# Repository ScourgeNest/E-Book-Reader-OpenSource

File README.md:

# 📖 OpenBook - Open-Source E-Book Reader

# Description
OpenBook is an open-source project aimed at developing an affordable and easily manufacturable e-book reader. This repository contains all the necessary hardware design files, including schematics, PCB layouts, 3D models, and manufacturing files.

#  Table of Contents

1. [📝 Description](#description)
2. [📜 Table of Contents](#table-of-contents)
3. [📂 Repository Contents](#repository-contents)
4. [🎯 Target Audience](#target-audience)
5. [🚀 Project Overview & Features](#project-overview--features)
6. [📊 E-Book Reader Diagram](#e-book-reader-diagram)
7. [📦 Bill of Materials (BOM)](#bill-of-materials-bom)
8. [🔧 Hardware Functionality Description](#hardware-functionality-description)
9. [🔌 Communication Interfaces](#communication-interfaces)
10. [⚡ Components and Estimated Power Consumption](#components-and-estimated-power-consumption)
11. [⚙️ ESP32-C6 Pin Usage Breakdown](#esp32-c6-pin-usage-breakdown)
12. [🛠️ Implementation Steps](#implementation-steps)
13. [🔧 Finalizing the Project](#finalizing-the-project)
14. [🖼️ Images](#images)

# Repository Contents
- 📡 **Schematic & PCB Design** → Circuit design files (`.sch`, `.brd`).
- 🏭 **Manufacturing Files** → Gerber files, Bill of Materials (BOM), Pick & Place files.
- 🏗️ **3D Model & Mechanical Design** → Full 3D assembly of the device, including PCB, battery, display, and casing.
- 📷 **Renders & Images** → Visual representations of the final device and PCB layout.
- 📜 **Documentation** → Detailed explanation of hardware architecture, component connections, and design decisions.

# Target Audience
This project is intended for hardware developers, electronics engineers, and open-source enthusiasts interested in PCB design, e-paper displays, and embedded systems.

## Project Overview & Features

### 📌 Project Goal
OpenBook aims to create an accessible and customizable open-source e-book reader that is affordable and easy to manufacture. By leveraging open hardware and software, we enable users to build and modify their own e-book readers while maintaining a low production cost.

### 🔹 Key Features
- **ESP32-C6 based** – Low-power microcontroller with Wi-Fi & Bluetooth connectivity.
- **E-paper Display** – Energy-efficient and easy on the eyes for long reading sessions.
- **Expandable Storage** – Supports microSD cards for storing a large collection of e-books.
- **USB-C Charging** – Modern and fast charging capability.
- **Open-Source Hardware** – Complete design files available for customization.
- **Compact and Lightweight** – Optimized design for portability and comfort.

### 🔧 System Architecture
The OpenBook device consists of four main components:
1. **PCB & Electronics** – The ESP32-C6 microcontroller, display driver, power management, and storage.
2. **E-paper Display Module** – A low-power display for efficient reading.
3. **Enclosure & Mechanical Design** – A 3D-printed or injection-molded case housing all components securely.
4. **Polymer Lithium-Ion Battery** – A rechargeable battery providing power to the device.

#  E-Book Reader Diagram

# Bill of Materials (BOM)

| 🔩 Component                                        | 🔗 Link                | 📄 Datasheet                        |
|--------------------------------------------------|-----------------------------------|-----------------------------------|
| ESP32-C6 WROOM-1-N8                              | [SnapMagic](https://www.snapeda.com/parts/ESP32-C6-WROOM-1-N8/Espressif+Systems/view-part/?ref=eda)         | [Datasheet](https://www.snapeda.com/parts/ESP32-C6-WROOM-1-N8/Espressif%20Systems/datasheet/)     |
| ESP32C6 Varistor 1812                            | [Mouser](https://ro.mouser.com/ProductDetail/EPCOS-TDK/B72520T0350K062?qs=dEfas%2FXlABIszF52uu7vrg%3D%3D)        | [Datasheet](https://www.tdk-electronics.tdk.com/inf/75/db/CTVS_14/Surge_protection_series.pdf)     |
| ESP32 WROVER 0805 Capacitor                      | [Mouser](https://ro.mouser.com/ProductDetail/KYOCERA-AVX/SD0805S020S1R0?qs=jCA%252BPfw4LHbpkAoSnwrdjw%3D%3D)         | [Datasheet](https://ro.mouser.com/datasheet/2/40/schottky-3165252.pdf)     |
| ESP32 WROVER BME680 Sensor                       | [SnapMagic](https://www.snapeda.com/parts/BME680/Bosch/view-part/?welcome=home)        | [Datasheet](https://www.snapeda.com/parts/BME680/Bosch%20Sensortec/datasheet/)     |
| ESP32 WROVER MCP73831 Power Management           | [Mouser](https://eu.mouser.com/ProductDetail/Microchip-Technology/MCP73831T-2ACI-OT?qs=yUQqVecv4qvbBQBGbHx0Mw%3D%3D)         | [Datasheet](https://eu.mouser.com/datasheet/2/268/MCP73831_Family_Data_Sheet_DS20001984H-3441711.pdf)     || ESP32 WROVER P-Channel MOSFET                    | [Component Search Engine](https://componentsearchengine.com/part-view/DMG2305UX-7/Diodes%20Incorporated)         | [Datasheet](https://www.diodes.com//assets/Datasheets/DMG2305UX.pdf)     |
| LED Chip 0603                                    | [SnapMagic](https://www.snapeda.com/parts/KP-1608SURCK/Kingbright/view-part/?ref=search&t=LED%200603)        | [Datasheet](https://www.snapeda.com/parts/KP-1608SURCK/Kingbright/datasheet/)     |
| SJ                                               | [GrabCad](https://grabcad.com/library/solder-jumpers-1)         | [Datasheet](https://www.youtube.com/watch?v=dQw4w9WgXcQ)     |
| LTSPICE Resistor 0402                            | [Component Search Engine](https://componentsearchengine.com/part-view/R0402%201%25%20100%20K%20(RC0402FR-07100KL)/YAGEO)        | [Datasheet](https://www.yageo.com/upload/media/product/products/datasheet/rchip/PYu-RC_Group_51_RoHS_L_12.pdf)     |
| RCL CPOL 3528                                    | [SnapMagic](https://www.snapeda.com/parts/TAJB475K025RNJ/AVX/view-part/?ref=dk&t=capacitor%203528&con_ref=None)        | [Datasheet](https://s3.amazonaws.com/snapeda/datasheet/TAJB475K025RNJ_AVX.pdf)     |
| 112A-TAAR-R03                                    | [Comet](https://store.comet.srl.ro/Catalogue/Product/43497/)         | [Datasheet](https://store.comet.bg/download-file.php?id=27596)     |
| Capacitor 0402                                   | [Component Search Engine](https://componentsearchengine.com/part-view/CC0402MRX5R5BB106/YAGEO)         | [Datasheet](https://componentsearchengine.com/Datasheets/2/CC0402MRX5R5BB106.pdf)     |
| 744043680 IND                                    | [Mouser](https://eu.mouser.com/ProductDetail/Wurth-Elektronik/744043680?qs=PGXP4M47uW6VkZq%252BkzjrHA%3D%3D)        | [Datasheet](https://www.we-online.com/components/products/datasheet/744043680.pdf)     |
| BD5229G-TR                                       | [Component Search Engine](https://componentsearchengine.com/part-view/BD5229G-TR/ROHM%20Semiconductor)         | [Datasheet](https://datasheet.datasheetarchive.com/originals/distributors/Datasheets_SAMA/f2b9741ef86007909f138d561a359946.pdf)     |
| Custom Button                                    | [Panasonic](https://industry.panasonic.com/global/en/products/control/switch/light-touch/number/evqpuj02k)        | [Datasheet](https://industry.panasonic.com/global/en/downloads?tab=catalog&small_g_cd=203&part_no=EVQPUJ02K&q=RVZRUFVKMDJLJTdDMTMlN0MyMDMlN0MzNDU5JTdDMSU3QyU3QzIlN0M%3D)     |
| CPH3225A                                         | [SnapMagic](https://www.snapeda.com/parts/CPH3225A/Seiko+Instruments/view-part/?ref=eda)         | [Datasheet](https://www.snapeda.com/parts/CPH3225A/Seiko%20Instruments/datasheet/)     |
| DS3231SN RTC                                     | [SnapMagic](https://www.snapeda.com/parts/DS3231SN%23/Analog+Devices/view-part/?ref=eda)        | [Datasheet](https://www.snapeda.com/parts/DS3231SN%23/Analog%20Devices/datasheet/)     |
| FH34SRJ-24S-0.5SH Connector                      | [Component Search Engine](https://componentsearchengine.com/part-view/FH34SRJ-24S-0.5SH(99)/Hirose)        | [Datasheet](https://www.hirose.com/en/product/document?clcode=CL0580-1255-6-99&productname=FH34SRJ-24S-0.5SH(99)&series=FH34SRJ&documenttype=2DDrawing&lang=en&documentid=0000990903)     |
| MAX17048G+T10 Battery Fuel Gauge                 | [SnapMagic](https://www.snapeda.com/parts/MAX17048G+T10/Analog+Devices/view-part/?ref=eda)         | [Datasheet](https://www.snapeda.com/parts/MAX17048G+T10/Analog%20Devices/datasheet/)     |
| MBR0530 Schottky Diode                           | [SnapMagic](https://www.snapeda.com/parts/MBR0530/Onsemi/view-part/?ref=eda)        | [Datasheet](https://www.snapeda.com/parts/MBR0530/ON%20Semiconductor/datasheet/)     |
| PGB1010603MR Inductor                            | [SnapMagic](https://www.snapeda.com/parts/PGB1010603MR/Littelfuse/view-part/?ref=eda)         | [Datasheet](https://www.snapeda.com/parts/PGB1010603MR/Littelfuse%20Inc./datasheet/)     |
| QWIIC Connector                                  | [Mouser](https://eu.mouser.com/ProductDetail/Adafruit/4208?qs=PzGy0jfpSMtbScLbr0L5dw%3D%3D)        | [Datasheet](https://www.youtube.com/watch?v=dQw4w9WgXcQ)     |
| USB4110-GF-A USB Hub                             | [Component Search Engine](https://componentsearchengine.com/part-view/USB4110-GF-A/GCT%20(GLOBAL%20CONNECTOR%20TECHNOLOGY))         | [Datasheet](https://gct.co/files/drawings/usb4110.pdf)     |
| SI1308EDL-T1-GE3 MOSFET                          | [SnapMagic](https://www.snapeda.com/parts/SI1308EDL-T1-GE3/Vishay+Siliconix/view-part/?ref=eda)        | [Datasheet](https://www.youtube.com/watch?v=dQw4w9WgXcQ)     |
| TPTP20R                                          | [Comet](https://easyeda.com/component/7524403feb2642ac9f9f26dfb93ceacf)         | [Datasheet](https://easyeda.com/component/7524403feb2642ac9f9f26dfb93ceacf)     |
| USBLC6-2SC6Y USB Surge Protection                | [SnapMagic](https://www.snapeda.com/parts/USBLC6-2SC6Y/STMicroelectronics/view-part/?ref=eda)        | [Datasheet](https://www.snapeda.com/parts/USBLC6-2SC6Y/STMicroelectronics/datasheet/)     |
| W25Q512JVEIQ Flash Memory                        | [SnapMagic](https://www.snapeda.com/parts/W25Q512JVEIQ/Winbond+Electronics/view-part/?ref=eda)         | [Datasheet](https://www.snapeda.com/parts/W25Q512JVEIQ/Winbond%20Electronics/datasheet/)     |
| XC6220A331MR-G Voltage Regulator                 | [Component Search Engine](https://componentsearchengine.com/part-view/XC6220A331MR-G/Torex)        | [Datasheet](https://product.torexsemi.com/system/files/series/xc6220.pdf)     |

# Hardware Functionality Description

## 1. 🔋 **Battery:**
   - **Model:** CELLEVIA BATTERIES LP584174
   - **Specifications:** 3.7V, 1800mAh
   - **Functionality:** Provides stable power for the entire device. The Li-Po battery is charged and monitored by a dedicated controller, ensuring longer battery life and protection against overcharging and deep discharge.

## 2. 🖥️ **E-Paper Display:**
   - **Model:** 7.5” e-Paper V2
   - **Revision:** 2.0 (2019/06/28)
   - **Functionality:** The e-paper display allows for extremely low power consumption, making it ideal for long-term text reading. It is controlled via an SPI interface and powered by an LDO (Low Dropout Regulator).

## 3. 🧠 **ESP32 C6:**
   - **Functionality:** The main microcontroller of the device, responsible for managing all hardware functions and communication between internal components. It connects to the display, sensors, SD card, external flash, and other peripheral modules.

## 4. 🌍 **Environmental Sensor BME688:**
   - **Interface:** I2C
   - **Functionality:** Measures temperature, humidity, pressure, and air quality. It provides environmental information and can contribute to adjusting the device's behavior based on the surrounding conditions.

## 5. ⏰ **RTC (Real-Time Clock) - DS3231SN:**
   - **Interface:** I2C
   - **Functionality:** Keeps accurate time and date even when the device is turned off. It is essential for synchronizing any time-related activities (e.g., saving progress or scheduling device wake-up).

## 6. ⚡ **Li-Po Charging Controller (MCP73831T):**
   - **Interface:** USB-C
   - **Functionality:** This module regulates the charging of the Li-Po battery, ensuring protection against overcharging and deep discharge. It is powered through the USB-C connector, which enables fast charging.

## 7. 💾 **SD Card Module:**
   - **Interface:** SPI
   - **Functionality:** Allows for the storage of files, including e-book documents, on an external SD card. This is essential for managing the reading files.

## 8. 🧠 **External NOR Flash 64MB:**
   - **Interface:** SPI
   - **Functionality:** Provides additional storage for the application files and device data.

## 9. 🛠️ **Test Pads and Qwiic/Stemma QT:**
   - **Functionality:** Test pads are used for debugging and testing, while the Qwiic/Stemma QT connectors enable easy addition of new modules through I2C or SPI interfaces.

## 10. 💡 **LDO Voltage Regulator:**
   - **Functionality:** Ensures a constant voltage supply to all modules, protecting them from input voltage fluctuations.

---

##  Communication Interfaces
   - **🟢 GPIO:** Used for managing physical buttons (e.g., reset button, power button).
   - **🔌 USB-C:** Enables battery charging and connection to a PC for data transfer.
   - **🔄 I2C:** Used for communication with the 🛰️ BME688 sensor and ⏰ DS3231SN RTC module.
   - **⚡ SPI:** Used to connect to the 💾 SD card, 📜 e-paper display, and 🔥 external flash, enabling fast data transfer.

#  Components and Estimated Power Consumption

Now that we have detailed the components of the project, we can approximate the energy consumption based on typical values for each component.

## 🔋 Components and Estimated Power Consumption

### 1️⃣ **Polymer Lithium-Ion Battery (CELLEVIA BATTERIES LP584174)**
   - **🔋 Voltage:** 3.7V  
   - **⚡ Capacity:** 1800mAh  
   - **⏳ Battery Life:** Depends on total consumption, but with a capacity of 1800mAh, the battery could power the device for several hours.

### 2️⃣ **ESP32 C6 (Main Processor)**
   - The ESP32 C6 has variable power consumption depending on usage:
     - 💤 **Idle mode:** ~0.1mA  
     - 📡 **Wi-Fi active:** ~200mA  
     - 🔵 **Bluetooth active:** ~150mA  
     - 🚀 **Max (under heavy load, e.g., during communication):** ~350mA  

   - **⚡ Assumed average consumption:** **150mA**

### 3️⃣ **📜 7.5” E-Paper Display**
   - **Typical consumption:** 30-50mA during screen updates (very low power when idle).
   - Assuming updates happen a few times per hour, an average consumption of **40mA** can be expected.

### 4️⃣ **🛰️ Environmental Sensor BME688**
   - **Typical consumption:** 2-3mA during measurement.
   - We estimate **2mA** for the BME688 sensor.

### 5️⃣ **⏰ RTC Module DS3231SN**
   - **Typical consumption:** 1-2mA
   - Assuming an active mode, we estimate **2mA**.

### 6️⃣ **🔄 Li-Po Battery Charging Controller (MCP73831T)**
   - **Power consumption:** Minimal during charging, so it is **negligible** for this estimate.

### 7️⃣ **💾 SD Card**
   - **Typical consumption:** 10-15mA during data access.
   - We estimate **12mA** for the SD card.

### 8️⃣ **🔥 External NOR Flash (64MB)**
   - **Typical consumption:** 20-30mA when reading data, lower in standby mode.
   - We estimate **25mA** for active usage.

---

## 📊 Total Power Consumption Estimation (Typical Configuration)

Assuming the ESP32 is continuously active with Wi-Fi, the e-paper display updates every 10 seconds, and the BME688 sensor is continuously measuring.

| ⚙️ Component                        | ⚡ Consumption (mA) |
|--------------------------------------|---------------------|
| 📡 **ESP32 C6 (Wi-Fi active)**       | 200mA              |
| 📜 **E-Paper Display (Updating)**    | 40mA               |
| 🛰️ **BME688 Sensor (measuring)**    | 2mA                |
| ⏰ **RTC Module (active)**           | 2mA                |
| 💾 **SD Card (in use)**              | 12mA               |
| 🔥 **External NOR Flash**            | 25mA               |

### ✅ **Total Consumption (Typical Use):**
⚡ **200mA** (ESP32) + **40mA** (Display) + **2mA** (BME688) + **2mA** (RTC) + **12mA** (SD Card) + **25mA** (NOR Flash) = **281mA**

---

## ⏳ **Estimating Battery Life**

Given that the battery has a capacity of **1800mAh**, and assuming a typical consumption of **281mA**, we can estimate the battery life:

📏 **Battery Life Calculation:**  
`Battery Life = Battery Capacity / Average Consumption`  
`Battery Life = 1800mAh / 281mA ≈ 6.41 hours`

## 📢 **Conclusion**

Under continuous usage (**Wi-Fi active, periodic e-paper updates, and sensor readings**), the estimated battery life is **~6.4 hours**. However, real-world performance may vary due to:

- 🔋 **Power-saving optimizations** (e.g., deep sleep mode on ESP32)  
- 🔄 **Lower update frequency for e-paper display**  
- 📡 **Disabling Wi-Fi/Bluetooth when not needed**  

For **longer battery life**, optimizing power consumption by using sleep modes, reducing display updates, and minimizing SD card writes will be crucial. 🚀🔋

# ESP32-C6 Pin Usage Breakdown

## 🔋 Power Connections
- **3V3 (Pin 2 & Top Right)** → Provides 3.3V power to the ESP32-C6 and connected components.
- **GND (Bottom Right)** → Ground connection for the circuit.

## 🔄 Boot and Reset Control
- **GPIO8 (Pin 15, IO/BOOT)** → Used for boot mode selection. Pulled down via a 10KΩ resistor.
- **RESET (Pin 3)** → Manual reset pin.

## 🔗 SPI Interface (For E-Paper Display & Flash)
- **MISO (Pin 27)** → Master-In Slave-Out, used for reading data from peripherals like the E-Paper Display.
- **MOSI (Pin 10)** → Master-Out Slave-In, used for sending data to peripherals.
- **SCK (Pin 7)** → Serial Clock, used for synchronizing SPI communication.
- **SS_SD (Pin 4)** → Likely used as a chip select (CS) for an SD card or another SPI peripheral.
- **EPD_CS (Pin 11)** → Chip select for the E-Paper Display.
- **FLASH_CS (Pin 12)** → Chip select for external Flash memory.

## 🖥️ E-Paper Display Control Signals
- **EPD_BUSY (Pin 26)** → Indicates when the E-Paper Display is busy.
- **EPD_DC (Pin 5)** → Data/Command control for the E-Paper Display.
- **EPD_RST (Pin 21)** → Reset pin for the E-Paper Display.
- **EPD_3V3_C (Pin 19)** → Likely an enable pin for EPD power.

## 📡 I2C Interface (For RTC and Sensors)
- **SDA (Pin 20)** → Data line for I2C communication.
- **SCL (Pin 21)** → Clock line for I2C communication.
- **I2C_PW (Pin 18)** → Likely a power enable signal for I2C devices.
- **INT_RTC (Pin 8)** → Interrupt signal from the RTC module.
- **RTC_RST (Pin 16)** → Reset line for the RTC module.

## 🔌 USB Communication
- **USB_D- (Pin 13)** & **USB_D+ (Pin 14)** → Differential data lines for USB communication.

## 📶 Serial Communication (UART)
- **TX (Pin 25)** → UART transmit pin.
- **RX (Pin 24)** → UART receive pin.

## ⚙️ Other GPIO Assignments
- **IO_CHANGE (Pin 23)** → Might be used as an interrupt or status pin for external components.

---

### 🛠️ Why These Pins?
This pin selection follows these principles:
- **SPI pins** (MISO, MOSI, SCK, CS) handle high-speed communication with the E-Paper Display and Flash.
- **I2C pins** (SDA, SCL) facilitate low-speed communication with sensors (RTC & environmental sensor).
- **Dedicated control pins** (EPD_BUSY, EPD_DC, etc.) ensure efficient E-Paper operation.
- **UART pins** (TX, RX) enable debugging or external serial communication.

This setup ensures proper functionality and efficient communication between components. Let me know if you need clarifications! 🚀

#  Implementation Steps  

## 🔧 Step 1: Component Placement and Schematic  
The first step was to place the components on the PCB and connect them according to the provided schematic. This step was crucial to ensure that all the components were correctly positioned and interconnected.  

## 📐 Step 2: PCB Layout and Compatibility with Case  
Once the components were placed, the second step was to arrange them on the PCB layout to fit the given casing. I made sure that the connectors and pins aligned properly with the case's openings for ports and buttons.  

## 🔌 Step 3: Routing the Connections  
The third step involved routing the connections between the components (wires), where I encountered my first challenge. Due to suboptimal component placement, I had to route some power lines using vias, which were also routed on the bottom layer of the PCB. Additionally, I used a relatively large number of vias. However, as an engineer, I recognized that things don't need to be perfect, so I moved forward with the process, compensating with extra attention to detail in later steps.  

## 🖥️ Step 4: 3D Models for Each Component  
With the electrical schematic and PCB layout complete, the next step was to import and attach 3D models for each component. I sourced the models from various platforms, such as SnapMagic, Mouser, Comet, Component Search Engine, etc. These models helped visualize how the components would fit together in the final product.  

## 🔋 Step 5: Battery and Display 3D Design  
At this point, I used the datasheet for the **Polymer Lithium-Ion Battery (CELLEVIA BATTERIES LP584174)** to create its 3D model for the PCB. Similarly, I applied the same process for the **7.5-inch e-Paper V2 display**, ensuring both components were accurately represented in the 3D design.  

## 🏗️ Step 6: Final Design Assembly  
With the 3D PCB design complete, along with all components in place, I moved on to assembling the full design of the **E-Book Reader**. This included the **PCB, battery, display, and casing**, resulting in the final product design.  

# Finalizing the Project  

To complete the entire project, I had to add the following files:  

## 🛠️ Hardware  
  - **📜 Schematic File (.sch)** - The electronic circuit diagram.  
  - **📏 Board File (.brd)** - The PCB layout with routed connections.  

## 🏭 Manufacturing  
  - **📂 Gerbers.zip** - Files for PCB fabrication.  
  - **📋 Bill of Materials File (.csv)** - List of components used.  
  - **📌 Pick and Place File (.csv)** - Component placement data for assembly.  

## 🎨 Mechanical  
  - **📎 3D File of the Complete Device (.step)** - Exploded view of the full assembly.  
  - **🖌️ 3D Fusion360 File** - Editable 3D model of the device.  

## 🖼️ Images  
  - **📸 Rendered Images** - High-quality visuals of the PCB and device.  

## 📄 Additional Files  
  - **📝 LICENSE** - GNU GENERAL PUBLIC LICENSE 2007.  
  - **📖 README.md** - Project documentation and implementation steps.  

# Images  

## 🎯 Final Product

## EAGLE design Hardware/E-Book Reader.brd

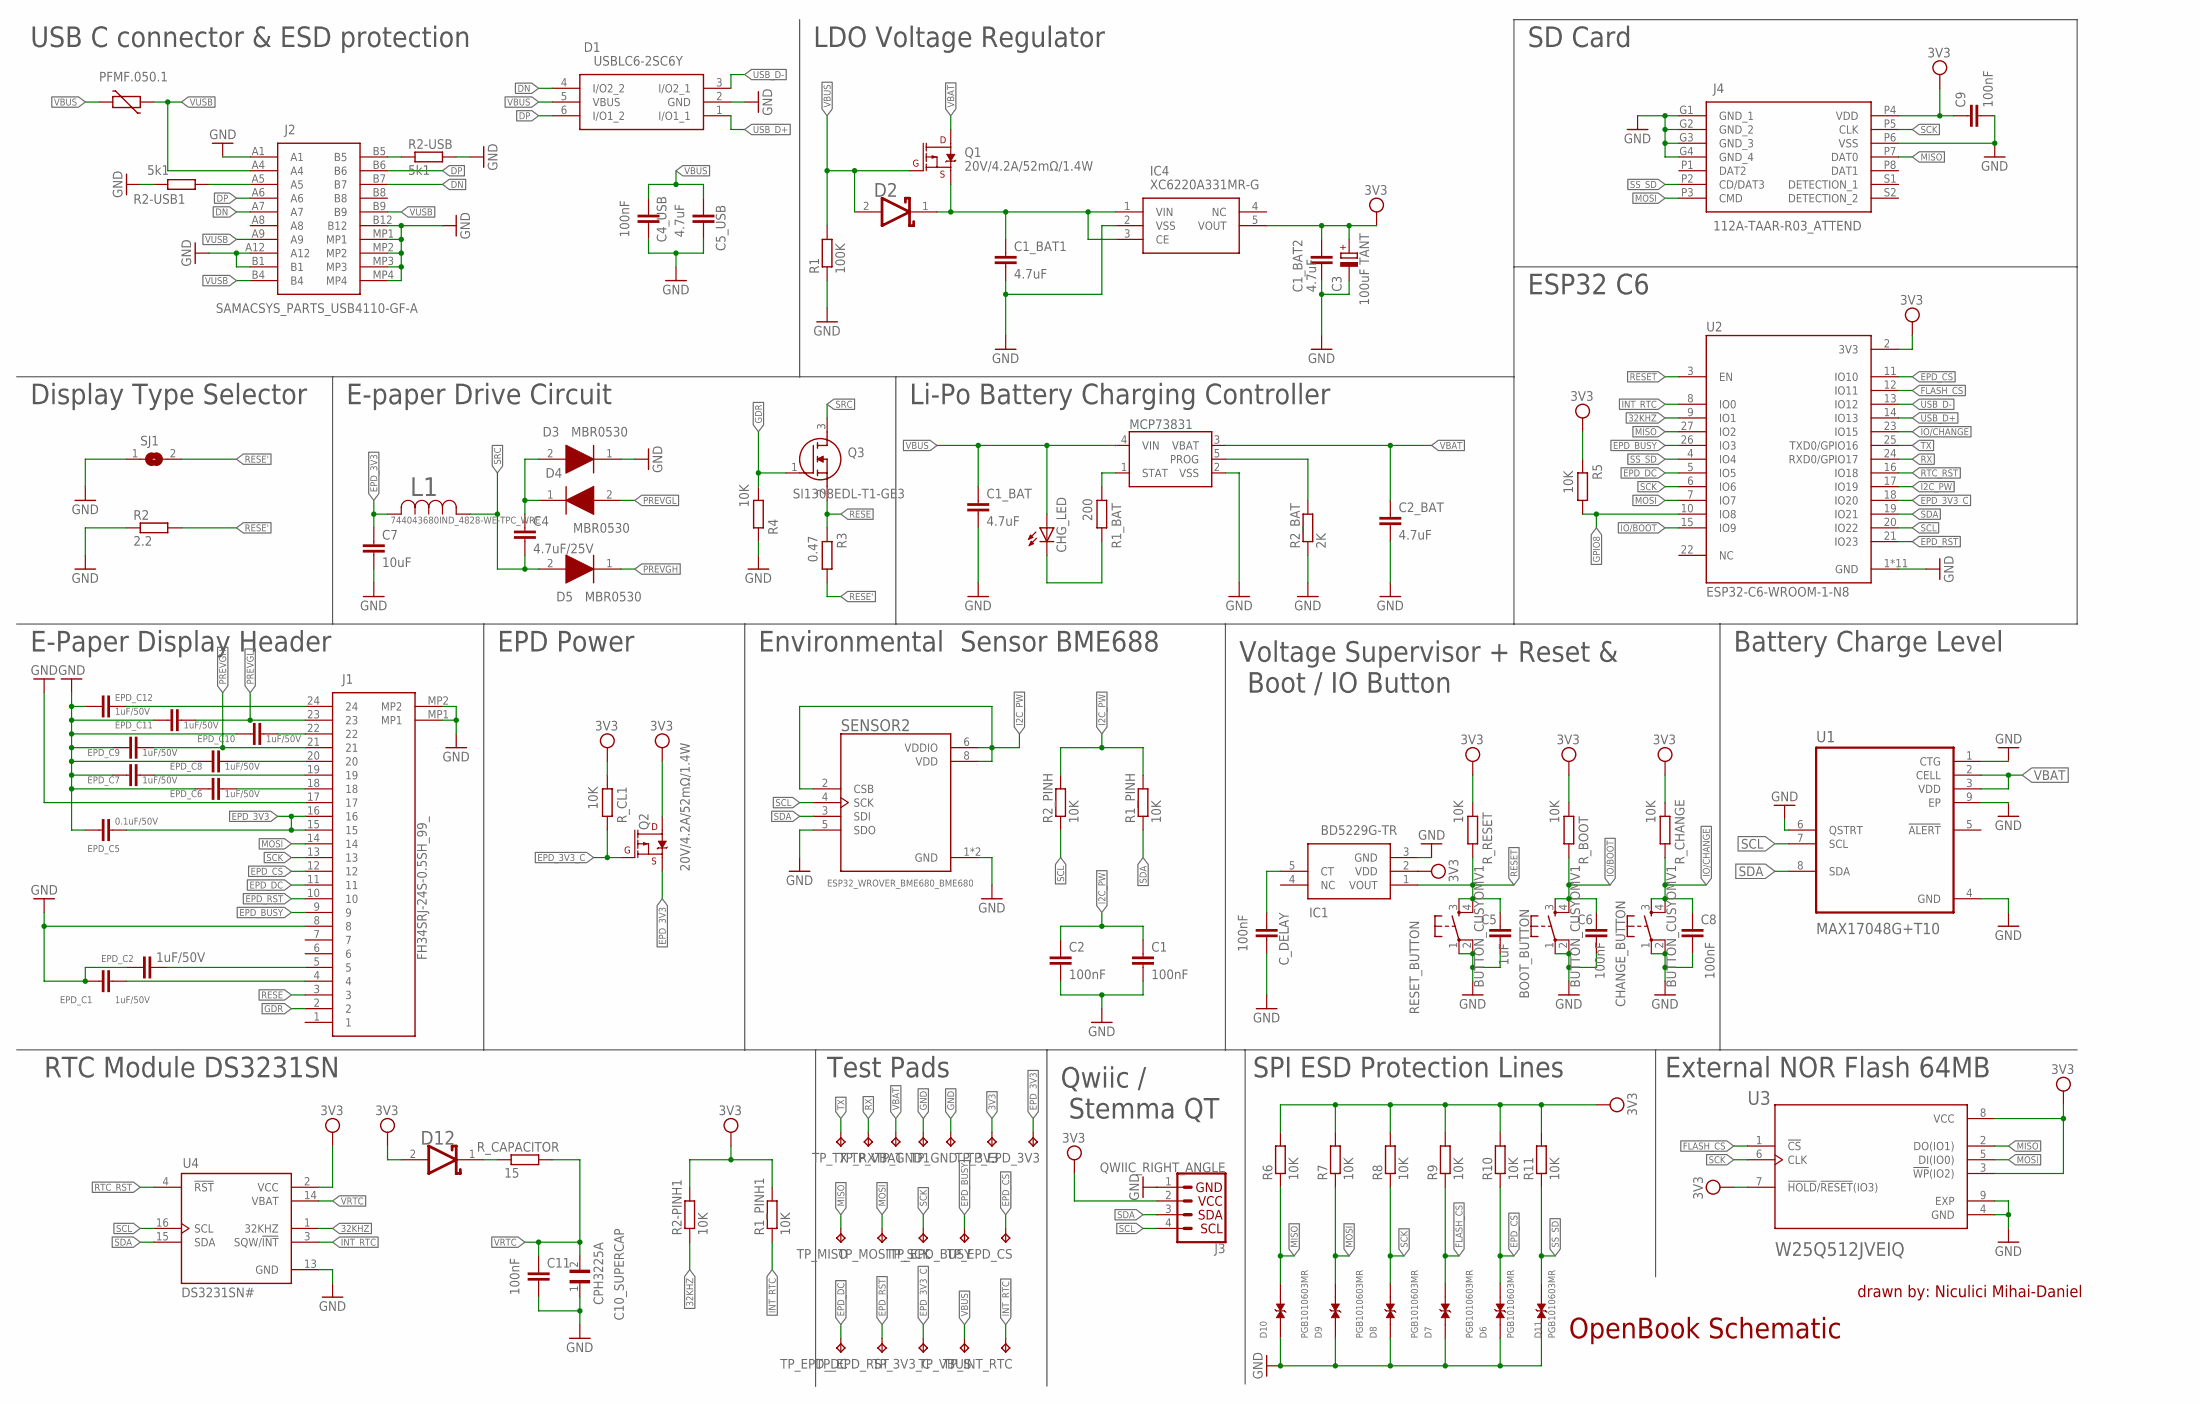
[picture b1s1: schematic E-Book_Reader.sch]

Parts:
BOOT_BUTTON: BUTTON_CUSYOMV1; MYBUTTON
C1, C2, C4_USB, C6, C8, C9, C11: 100nF; ESP32_WROVER_EAGLE-LTSPICE_C0402
C1_BAT, C1_BAT1, C1_BAT2, C2_BAT, C5_USB: 4.7uF; ESP32_WROVER_EAGLE-LTSPICE_C0402
C3: 100uF TANT; RCL_CT3528
C4: 4.7uF/25V; ESP32_WROVER_EAGLE-LTSPICE_C0402
C5: 1uF; ESP32_WROVER_EAGLE-LTSPICE_C0402
C7: 10uF; ESP32_WROVER_EAGLE-LTSPICE_C0402
C10_SUPERCAP: CPH3225A; CAPCP3225X100N
CHANGE_BUTTON: BUTTON_CUSYOMV1; MYBUTTON
CHG_LED: ADAFRUIT_LEDCHIP-LED0603; ADAFRUIT_CHIP-LED0603
C_DELAY: 100nF; ESP32_WROVER_EAGLE-LTSPICE_C0402
D1: USBLC6-2SC6Y; SOT95P280X145-6N
D2, D12: ESP32_WROVER_AVX---SD0805S020S1R0_AVX_SD0805S020S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; ESP32_WROVER_AVX---SD0805S020S1R0_AVX_SD0805S020S1R0_0
D3, D4, D5: MBR0530; SOD3716X135N
D6, D7, D8, D9, D10, D11: PGB1010603MR; DIOC1608X36N
EPD_C1, EPD_C2, EPD_C6, EPD_C7, EPD_C8, EPD_C9, EPD_C10, EPD_C11, EPD_C12: 1uF/50V; ESP32_WROVER_EAGLE-LTSPICE_C0402
EPD_C5: 0.1uF/50V; ESP32_WROVER_EAGLE-LTSPICE_C0402
IC1: BD5229G-TR; SOT95P280X125-5N
IC4: XC6220A331MR-G; SOT95P280X120-5N
J1: FH34SRJ-24S-0.5SH_99_; FH34SRJ24S05SH99
J2: SAMACSYS_PARTS_USB4110-GF-A; SAMACSYS_PARTS_USB4110GFA
J3: QWIIC_RIGHT_ANGLE; JST04_1MM_RA
J4: 112A-TAAR-R03_ATTEND; 112ATAARR03ATTEND
L1: 744043680IND_4828-WE-TPC_WRE; IND_4828-WE-TPC_WRE
MCP73831: ESP32_WROVER_SPARKFUN-IC-POWER_MCP73831; ESP32_WROVER_SPARKFUN-IC-POWER_SOT23-5
PFMF.050.1: ESP32C6_VARISTORCN1812; ESP32C6_VARISTOR_CT/CN1812
Q1, Q2: 20V/4.2A/52mΩ/1.4W; ESP32_WROVER_SPARKFUN-DISCRETESEMI_SOT23-3
Q3: SI1308EDL-T1-GE3; SOT65P210X110-3N
R1: 100K; ESP32_WROVER_EAGLE-LTSPICE_R0402
R1_BAT: 200; ESP32_WROVER_EAGLE-LTSPICE_R0402
R1_PINH, R1_PINH1, R2-PINH1, R2_PINH, R4, R5, R6, R7, R8, R9, R10, R11: 10K; ESP32_WROVER_EAGLE-LTSPICE_R0402
R2: 2.2; ESP32_WROVER_EAGLE-LTSPICE_R0402
R2-USB, R2-USB1: 5k1; ESP32_WROVER_EAGLE-LTSPICE_R0402
R2_BAT: 2K; ESP32_WROVER_EAGLE-LTSPICE_R0402
R3: 0.47; ESP32_WROVER_EAGLE-LTSPICE_R0402
RESET_BUTTON: BUTTON_CUSYOMV1; MYBUTTON
R_BOOT: 10K; ESP32_WROVER_EAGLE-LTSPICE_R0402
R_CAPACITOR: 15; ESP32_WROVER_EAGLE-LTSPICE_R0402
R_CHANGE: 10K; ESP32_WROVER_EAGLE-LTSPICE_R0402
R_CL1: 10K; ESP32_WROVER_EAGLE-LTSPICE_R0402
R_RESET: 10K; ESP32_WROVER_EAGLE-LTSPICE_R0402
SENSOR2: ESP32_WROVER_BME680_BME680; ESP32_WROVER_BME680_PSON80P300X300X100-8N
SJ1: SJ
TP_3V3, TP_3V3_C: TPTP20R; TP20R
TP_EPD_3V3: TPTP20R; TP20R
TP_EPD_BUSY: TPTP20R; TP20R
TP_EPD_CS: TPTP20R; TP20R
TP_EPD_DC: TPTP20R; TP20R
TP_EPD_RST: TPTP20R; TP20R
TP_GND, TP_GND1: TPTP20R; TP20R
TP_INT_RTC: TPTP20R; TP20R
TP_MISO: TPTP20R; TP20R
TP_MOSI: TPTP20R; TP20R
TP_RX: TPTP20R; TP20R
TP_SCK: TPTP20R; TP20R
TP_TX: TPTP20R; TP20R
TP_VBAT: TPTP20R; TP20R
TP_VBUS: TPTP20R; TP20R
U1: MAX17048G+T10; SON50P200X200X80-9N
U2: ESP32-C6-WROOM-1-N8; XCVR_ESP32-C6-WROOM-1-N8
U3: W25Q512JVEIQ; SON127P600X800X80-9N
U4: DS3231SN#; SOIC127P1032X265-16N

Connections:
3V3: C1_BAT2.1, C3.+, C9.1, D12.2 (ANODE), IC1.2 (VDD), IC4.5 (VOUT), J3.2, J4.P4 (VDD), Q2.3 (D), R1_PINH1.2, R2-PINH1.2, R5.2, R6.2, R7.2, R8.2, R9.2, R10.2, R11.2, R_BOOT.2, R_CHANGE.2, R_CL1.2, R_RESET.2, TP_3V3.TP, U2.2 (3V3), U3.3 (!WP!(IO2)), U3.7 (!HOLD!/!RESET!(IO3)), U3.8 (VCC), U4.2 (VCC)
32KHZ: R2-PINH1.1, U2.9 (IO1), U4.1 (32KHZ)
DN: D1.4 (I/O2_2), J2.A7, J2.B7
DP: D1.6 (I/O1_2), J2.A6, J2.B6
EPD_3V3: C7.1, EPD_C5.1, J1.15, J1.16, L1.2, Q2.2 (S), TP_EPD_3V3.TP
EPD_3V3_C: Q2.1 (G), R_CL1.1, TP_3V3_C.TP, U2.18 (IO20)
EPD_BUSY: J1.9, TP_EPD_BUSY.TP, U2.26 (IO3)
EPD_CS: D6.2, J1.12, R10.1, TP_EPD_CS.TP, U2.11 (IO10)
EPD_DC: J1.11, TP_EPD_DC.TP, U2.5 (IO5)
EPD_RST: J1.10, TP_EPD_RST.TP, U2.21 (IO23)
FLASH_CS: D7.2, R9.1, U2.12 (IO11), U3.1 (!CS)
GDR: J1.2, Q3.1 (G), R4.2
GND: BOOT_BUTTON.1, BOOT_BUTTON.2, C1.2, C1_BAT.2, C1_BAT1.2, C1_BAT2.2, C2.2, C2_BAT.2, C3.-, C4_USB.2, C5.2, C5_USB.2, C6.2, C7.2, C8.2, C9.2, C10_SUPERCAP.1, C11.2, CHANGE_BUTTON.1, CHANGE_BUTTON.2, C_DELAY.2, D1.2 (GND), D3.1 (K), D6.1, D7.1, D8.1, D9.1, D10.1, D11.1, EPD_C1.2, EPD_C2.2, EPD_C5.2, EPD_C6.2, EPD_C7.2, EPD_C8.2, EPD_C9.2, EPD_C10.2, EPD_C11.2, EPD_C12.2, IC1.3 (GND), IC4.2 (VSS), J1.8, J1.17, J1.MP1, J1.MP2, J2.A1, J2.A12, J2.B1, J2.B12, J2.MP1, J2.MP2, J2.MP3, J2.MP4, J3.1, J4.G1 (GND_1), J4.G2 (GND_2), J4.G3 (GND_3), J4.G4 (GND_4), J4.P6 (VSS), MCP73831.2 (VSS), R1.1, R2.1, R2-USB.2, R2-USB1.1, R2_BAT.1, R4.1, RESET_BUTTON.1, RESET_BUTTON.2, SENSOR2.1 (GND), SENSOR2.5 (SDO), SENSOR2.7 (GND), SJ1.1, TP_GND.TP, TP_GND1.TP, U1.1 (CTG), U1.4 (GND), U1.6 (QSTRT), U1.9 (EP), U2.1 (GND), U2.28 (GND), U2.29_1 (GND), U2.29_2 (GND), U2.29_3 (GND), U2.29_4 (GND), U2.29_5 (GND), U2.29_6 (GND), U2.29_7 (GND), U2.29_8 (GND), U2.29_9 (GND), U3.4 (GND), U3.9 (EXP), U4.13 (GND)
GPIO8: R5.1, U2.10 (IO8)
I2C_PW: C1.1, C2.1, R1_PINH.2, R2_PINH.2, SENSOR2.2 (CSB), SENSOR2.6 (VDDIO), SENSOR2.8 (VDD), U2.17 (IO19)
INT_RTC: R1_PINH1.1, TP_INT_RTC.TP, U2.8 (IO0), U4.3 (SQW/!INT)
IO/BOOT: BOOT_BUTTON.3, BOOT_BUTTON.4, C6.1, R_BOOT.1, U2.15 (IO9)
IO/CHANGE: C8.1, CHANGE_BUTTON.3, CHANGE_BUTTON.4, R_CHANGE.1, U2.23 (IO15)
MISO: D10.2, J4.P7 (DAT0), R6.1, TP_MISO.TP, U2.27 (IO2), U3.2 (DO(IO1))
MOSI: D9.2, J1.14, J4.P3 (CMD), R7.1, TP_MOSI.TP, U2.7 (IO7), U3.5 (DI(IO0))
PREVGH: D5.1 (K), EPD_C9.1, J1.21
PREVGL: D4.2 (A), EPD_C11.1, J1.23
P_NET_1: J2.A5, R2-USB1.2
P_NET_2: C1_BAT1.1, D2.1 (CATHODE), IC4.1 (VIN), IC4.3 (CE), Q1.2 (S)
P_NET_3: EPD_C12.1, J1.24
P_NET_5: EPD_C10.1, J1.22
P_NET_7: EPD_C8.1, J1.20
P_NET_8: EPD_C7.1, J1.19
P_NET_9: EPD_C6.1, J1.18
P_NET_10: EPD_C2.1, J1.5
P_NET_11: EPD_C1.1, J1.4
P_NET_12: C_DELAY.1, IC1.5 (CT)
P_NET_13: D12.1 (CATHODE), R_CAPACITOR.1
P_NET_14: MCP73831.5 (PROG), R2_BAT.2
P_NET_15: MCP73831.1 (STAT), R1_BAT.2
P_NET_16: CHG_LED.C, R1_BAT.1
P_NET_17: C4.1, D3.2 (A), D4.1 (K)
P_NET_18: J2.B5, R2-USB.1
RESE: J1.3, Q3.2 (S), R3.2
RESE': R2.2, R3.1, SJ1.2
RESET: C5.1, IC1.1 (VOUT), RESET_BUTTON.3, RESET_BUTTON.4, R_RESET.1, U2.3 (EN)
RTC_RST: U2.16 (IO18), U4.4 (!RST)
RX: TP_RX.TP, U2.24 (RXD0/GPIO17)
SCK: D8.2, J1.13, J4.P5 (CLK), R8.1, TP_SCK.TP, U2.6 (IO6), U3.6 (CLK)
SCL: J3.4, R2_PINH.1, SENSOR2.4 (SCK), U1.7 (SCL), U2.20 (IO22), U4.16 (SCL)
SDA: J3.3, R1_PINH.1, SENSOR2.3 (SDI), U1.8 (SDA), U2.19 (IO21), U4.15 (SDA)
SRC: C4.2, D5.2 (A), L1.1, Q3.3 (D)
SS_SD: D11.2, J4.P2 (CD/DAT3), R11.1, U2.4 (IO4)
TX: TP_TX.TP, U2.25 (TXD0/GPIO16)
USB_D+: D1.1 (I/O1_1), U2.14 (IO13)
USB_D-: D1.3 (I/O2_1), U2.13 (IO12)
VBAT: C2_BAT.1, MCP73831.3 (VBAT), Q1.3 (D), TP_VBAT.TP, U1.2 (CELL), U1.3 (VDD)
VBUS: C1_BAT.1, C4_USB.1, C5_USB.1, CHG_LED.A, D1.5 (VBUS), D2.2 (ANODE), MCP73831.4 (VIN), PFMF.050.1.2, Q1.1 (G), R1.2, TP_VBUS.TP
VRTC: C10_SUPERCAP.2, C11.1, R_CAPACITOR.2, U4.14 (VBAT)
VUSB: J2.A4, J2.A9, J2.B4, J2.B9, PFMF.050.1.1

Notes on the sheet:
USB C connector & ESD protection
LDO Voltage Regulator
SD Card
ESP32 C6
Display Type Selector
E-paper Drive Circuit
Li-Po Battery Charging Controller
E-Paper Display Header
EPD Power
Environmental Sensor BME688
Voltage Supervisor + Reset & Boot / IO Button
Battery Charge Level
RTC Module DS3231SN
Test Pads
Qwiic / Stemma QT
SPI ESD Protection Lines
External NOR Flash 64MB
OpenBook Schematic
drawn by: Niculici Mihai-Daniel

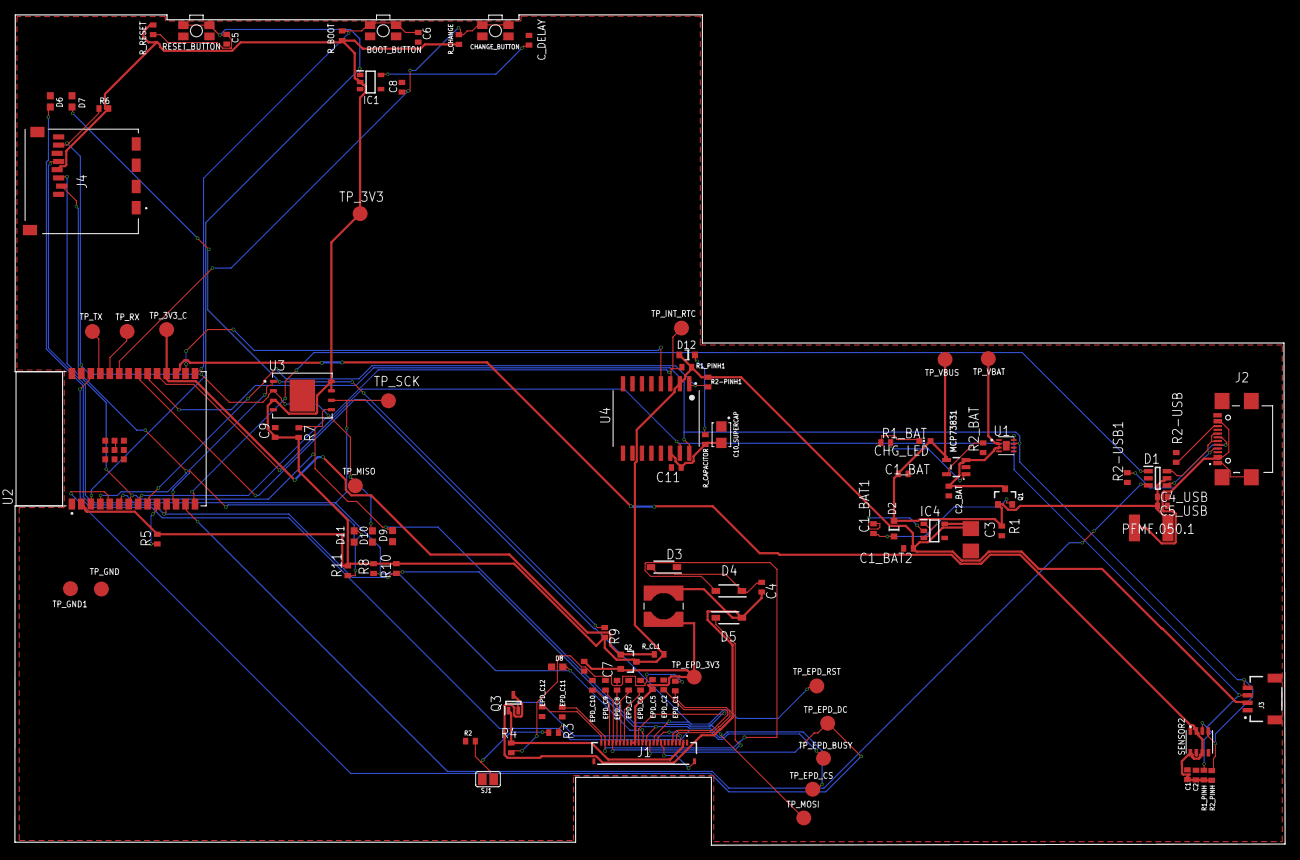
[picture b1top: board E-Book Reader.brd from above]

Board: 2 copper layers, 170.3 x 111.4 mm, 103 parts (0 on the bottom side), 55 nets.

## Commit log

2025-04-03 Adding Images of the E-Book Reader
2025-04-03 Adding gerber files
2025-04-03 Adding Pick and Place file
2025-04-03 Adding Bill of Materials
2025-04-03 Adding GNU LICENSE
2025-04-03 Schematic File
2025-04-03 Board File
2025-04-03 Exploded_View
2025-04-03 3D Device Model
2025-04-03 E-Book Reader Diagram + README
2025-04-14 Update Images After Fixing Issues
2025-04-14 Updated Schematic and PCB After Fixing Issues
2025-04-14 Updated PnP and gerber Files After Fixing Issues
2025-04-14 Updated Mechanical Folder after fixing Issues
2025-04-15 Images Updated
2025-04-15 Final Version

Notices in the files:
README.md:
- **📝 LICENSE** - GNU GENERAL PUBLIC LICENSE 2007.
parts and their libraries:
COPYRIGHT: Copyright (C) 2024 Ultra Librarian. All rights reserved.
